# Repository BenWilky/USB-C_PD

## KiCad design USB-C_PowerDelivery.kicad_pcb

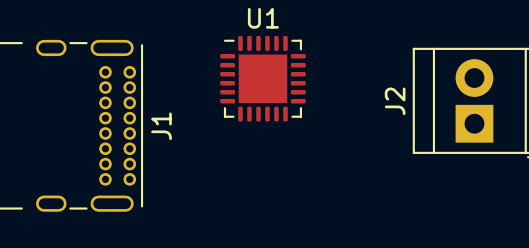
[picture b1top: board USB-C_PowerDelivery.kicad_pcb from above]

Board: 2 copper layers, 3 parts (0 on the bottom side), 6 nets, no tracks yet.

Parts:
J1: USB_C_Receptacle_USB2.0; USB_C_Receptacle_GCT_USB4085
J2: Screw_Terminal_01x02; TerminalBlock_TE_282834-2_1x02_P2.54mm_Horizontal
U1: STUSB4500QTR; QFN-24-1EP_4x4mm_P0.5mm_EP2.7x2.7mm

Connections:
CC1: J1.A5, U1.1, U1.2
CC2: J1.B5, U1.4, U1.5
D+: J1.A6, J1.B6
D-: J1.A7, J1.B7
GND: J1.A1, J1.A12, J1.B1, J1.B12, U1.10, U1.25
VDD: J1.A4, J1.A9, J1.B4, J1.B9
